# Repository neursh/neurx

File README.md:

# Neurx

A mechanical keyboard aiming for maximum customizability.

## Features (WIP)

- A 75% keyboard (with numpad mode can be toggled).
- 4 programmable keys + 1 knob.
- Firmware is compatible with Raspberry Pi Pico (and Pico W), written in Rust.
- Plug and play, no driver needed, with 1000Hz polling rate.
- Software for Windows, provides better control over programmable keys.

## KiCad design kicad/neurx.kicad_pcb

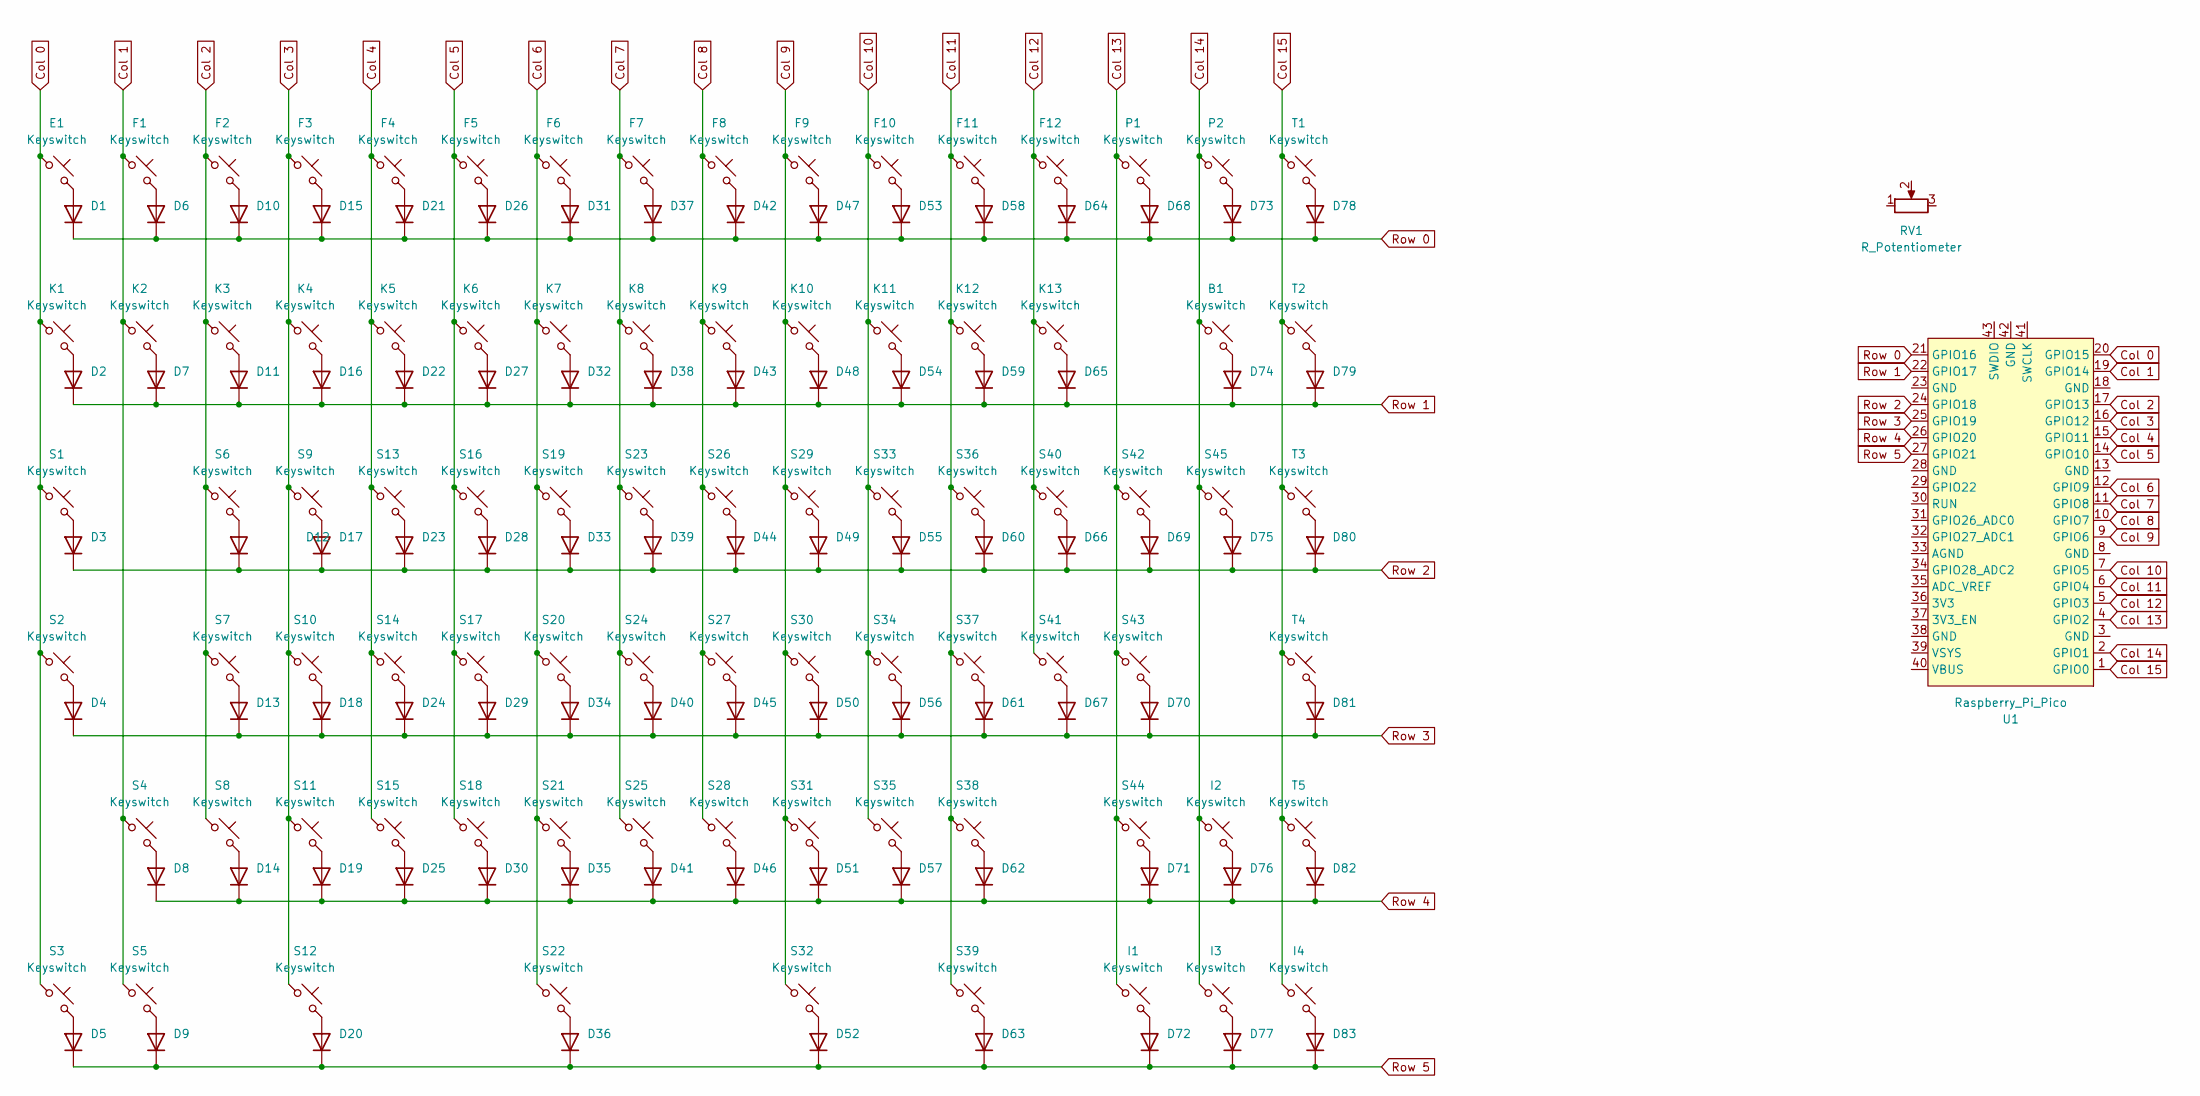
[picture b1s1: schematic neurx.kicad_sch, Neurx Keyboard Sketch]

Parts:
B1: Keyswitch; MX_PCB_2.00u
D1, D2, D3, D4, D5, D6, D7, D8, D9, D10, D11, D12, D13, D14, D15, D16, D17, D18, D19, D20, D21, D22, D23, D24, D25, D26, D27, D28, D29, D30, D31, D32, D33, D34, D35, D36, D37, D38, D39, D40, D41, D42, D43, D44, D45, D46, D47, D48, D49, D50, D51, D52, D53, D54, D55, D56, D57, D58, D59, D60, D61, D62, D63, D64, D65, D66, D67, D68, D69, D70, D71, D72, D73, D74, D75, D76, D77, D78, D79, D80, D81, D82, D83: Diode; Diode_DO-35
E1: Keyswitch; MX_PCB_1.00u
F1, F2, F3, F4, F5, F6, F7, F8, F9, F10, F11, F12: Keyswitch; MX_PCB_1.00u
I1, I2, I3, I4: Keyswitch; MX_PCB_1.00u
K1, K2, K3, K4, K5, K6, K7, K8, K9, K10, K11, K12, K13: Keyswitch; MX_PCB_1.00u
P1, P2: Keyswitch; MX_PCB_1.00u
RV1: R_Potentiometer
S1, S45: Keyswitch; MX_PCB_1.50u
S2, S44: Keyswitch; MX_PCB_1.75u
S3, S5, S12, S32, S39: Keyswitch; MX_PCB_1.25u
S4, S43: Keyswitch; MX_PCB_2.25u
S6, S7, S8, S9, S10, S11, S13, S14, S15, S16, S17, S18, S19, S20, S21, S23, S24, S25, S26, S27, S28, S29, S30, S31, S33, S34, S35, S36, S37, S38, S40, S41, S42: Keyswitch; MX_PCB_1.00u
S22: Keyswitch; MX_PCB_6.25u
T1, T2, T3, T4, T5: Keyswitch; MX_PCB_1.00u
U1: Raspberry_Pi_Pico

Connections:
Col 0: E1.1, K1.1, S1.1, S2.1, S3.1, U1.20 (GPIO15)
Col 1: F1.1, K2.1, S4.1, S5.1, U1.19 (GPIO14)
Col 2: F2.1, K3.1, S6.1, S7.1, S8.1, U1.17 (GPIO13)
Col 3: F3.1, K4.1, S9.1, S10.1, S11.1, S12.1, U1.16 (GPIO12)
Col 4: F4.1, K5.1, S13.1, S14.1, S15.1, U1.15 (GPIO11)
Col 5: F5.1, K6.1, S16.1, S17.1, S18.1, U1.14 (GPIO10)
Col 6: F6.1, K7.1, S19.1, S20.1, S21.1, S22.1, U1.12 (GPIO9)
Col 7: F7.1, K8.1, S23.1, S24.1, S25.1, U1.11 (GPIO8)
Col 8: F8.1, K9.1, S26.1, S27.1, S28.1, U1.10 (GPIO7)
Col 9: F9.1, K10.1, S29.1, S30.1, S31.1, S32.1, U1.9 (GPIO6)
Col 10: F10.1, K11.1, S33.1, S34.1, S35.1, U1.7 (GPIO5)
Col 11: F11.1, K12.1, S36.1, S37.1, S38.1, S39.1, U1.6 (GPIO4)
Col 12: F12.1, K13.1, S40.1, S41.1, U1.5 (GPIO3)
Col 13: I1.1, P1.1, S42.1, S43.1, S44.1, U1.4 (GPIO2)
Col 14: B1.1, I2.1, I3.1, P2.1, S45.1, U1.2 (GPIO1)
Col 15: I4.1, T1.1, T2.1, T3.1, T4.1, T5.1, U1.1 (GPIO0)
unnamed: D1.2 (A), E1.2
unnamed: D2.2 (A), K1.2
unnamed: D3.2 (A), S1.2
unnamed: D4.2 (A), S2.2
unnamed: D5.2 (A), S3.2
unnamed: D6.2 (A), F1.2
unnamed: D7.2 (A), K2.2
unnamed: D8.2 (A), S4.2
unnamed: D9.2 (A), S5.2
unnamed: D10.2 (A), F2.2
unnamed: D11.2 (A), K3.2
unnamed: D12.2 (A), S6.2
unnamed: D13.2 (A), S7.2
unnamed: D14.2 (A), S8.2
unnamed: D15.2 (A), F3.2
unnamed: D16.2 (A), K4.2
unnamed: D17.2 (A), S9.2
unnamed: D18.2 (A), S10.2
unnamed: D19.2 (A), S11.2
unnamed: D20.2 (A), S12.2
unnamed: D21.2 (A), F4.2
unnamed: D22.2 (A), K5.2
unnamed: D23.2 (A), S13.2
unnamed: D24.2 (A), S14.2
unnamed: D25.2 (A), S15.2
unnamed: D26.2 (A), F5.2
unnamed: D27.2 (A), K6.2
unnamed: D28.2 (A), S16.2
unnamed: D29.2 (A), S17.2
unnamed: D30.2 (A), S18.2
unnamed: D31.2 (A), F6.2
unnamed: D32.2 (A), K7.2
unnamed: D33.2 (A), S19.2
unnamed: D34.2 (A), S20.2
unnamed: D35.2 (A), S21.2
unnamed: D36.2 (A), S22.2
unnamed: D37.2 (A), F7.2
unnamed: D38.2 (A), K8.2
unnamed: D39.2 (A), S23.2
unnamed: D40.2 (A), S24.2
unnamed: D41.2 (A), S25.2
unnamed: D42.2 (A), F8.2
unnamed: D43.2 (A), K9.2
unnamed: D44.2 (A), S26.2
unnamed: D45.2 (A), S27.2
unnamed: D46.2 (A), S28.2
unnamed: D47.2 (A), F9.2
unnamed: D48.2 (A), K10.2
unnamed: D49.2 (A), S29.2
unnamed: D50.2 (A), S30.2
unnamed: D51.2 (A), S31.2
unnamed: D52.2 (A), S32.2
unnamed: D53.2 (A), F10.2
unnamed: D54.2 (A), K11.2
unnamed: D55.2 (A), S33.2
unnamed: D56.2 (A), S34.2
unnamed: D57.2 (A), S35.2
unnamed: D58.2 (A), F11.2
unnamed: D59.2 (A), K12.2
unnamed: D60.2 (A), S36.2
unnamed: D61.2 (A), S37.2
unnamed: D62.2 (A), S38.2
unnamed: D63.2 (A), S39.2
unnamed: D64.2 (A), F12.2
unnamed: D65.2 (A), K13.2
unnamed: D66.2 (A), S40.2
unnamed: D67.2 (A), S41.2
unnamed: D68.2 (A), P1.2
unnamed: D69.2 (A), S42.2
unnamed: D70.2 (A), S43.2
unnamed: D71.2 (A), S44.2
unnamed: D72.2 (A), I1.2
unnamed: D73.2 (A), P2.2
unnamed: B1.2, D74.2 (A)
unnamed: D75.2 (A), S45.2
unnamed: D76.2 (A), I2.2
unnamed: D77.2 (A), I3.2
unnamed: D78.2 (A), T1.2
unnamed: D79.2 (A), T2.2
unnamed: D80.2 (A), T3.2
unnamed: D81.2 (A), T4.2
unnamed: D82.2 (A), T5.2
unnamed: D83.2 (A), I4.2
Row 0: D1.1 (K), D6.1 (K), D10.1 (K), D15.1 (K), D21.1 (K), D26.1 (K), D31.1 (K), D37.1 (K), D42.1 (K), D47.1 (K), D53.1 (K), D58.1 (K), D64.1 (K), D68.1 (K), D73.1 (K), D78.1 (K), U1.21 (GPIO16)
Row 1: D2.1 (K), D7.1 (K), D11.1 (K), D16.1 (K), D22.1 (K), D27.1 (K), D32.1 (K), D38.1 (K), D43.1 (K), D48.1 (K), D54.1 (K), D59.1 (K), D65.1 (K), D74.1 (K), D79.1 (K), U1.22 (GPIO17)
Row 2: D3.1 (K), D12.1 (K), D17.1 (K), D23.1 (K), D28.1 (K), D33.1 (K), D39.1 (K), D44.1 (K), D49.1 (K), D55.1 (K), D60.1 (K), D66.1 (K), D69.1 (K), D75.1 (K), D80.1 (K), U1.24 (GPIO18)
Row 3: D4.1 (K), D13.1 (K), D18.1 (K), D24.1 (K), D29.1 (K), D34.1 (K), D40.1 (K), D45.1 (K), D50.1 (K), D56.1 (K), D61.1 (K), D67.1 (K), D70.1 (K), D81.1 (K), U1.25 (GPIO19)
Row 4: D8.1 (K), D14.1 (K), D19.1 (K), D25.1 (K), D30.1 (K), D35.1 (K), D41.1 (K), D46.1 (K), D51.1 (K), D57.1 (K), D62.1 (K), D71.1 (K), D76.1 (K), D82.1 (K), U1.26 (GPIO20)
Row 5: D5.1 (K), D9.1 (K), D20.1 (K), D36.1 (K), D52.1 (K), D63.1 (K), D72.1 (K), D77.1 (K), D83.1 (K), U1.27 (GPIO21)

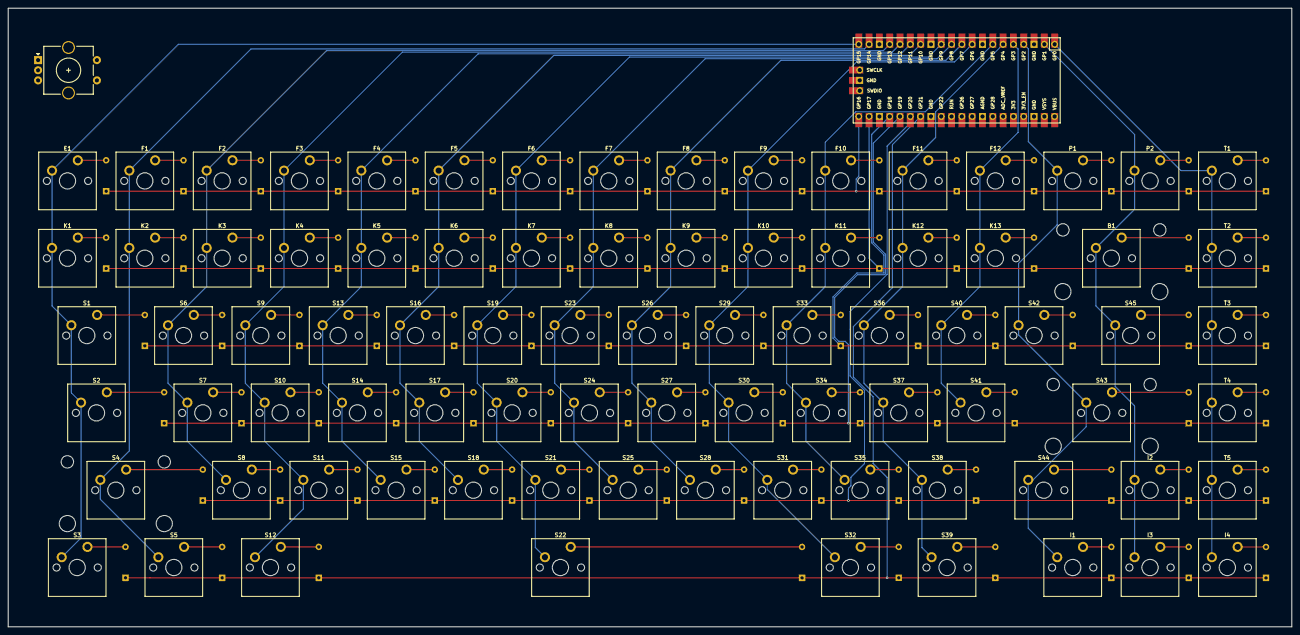
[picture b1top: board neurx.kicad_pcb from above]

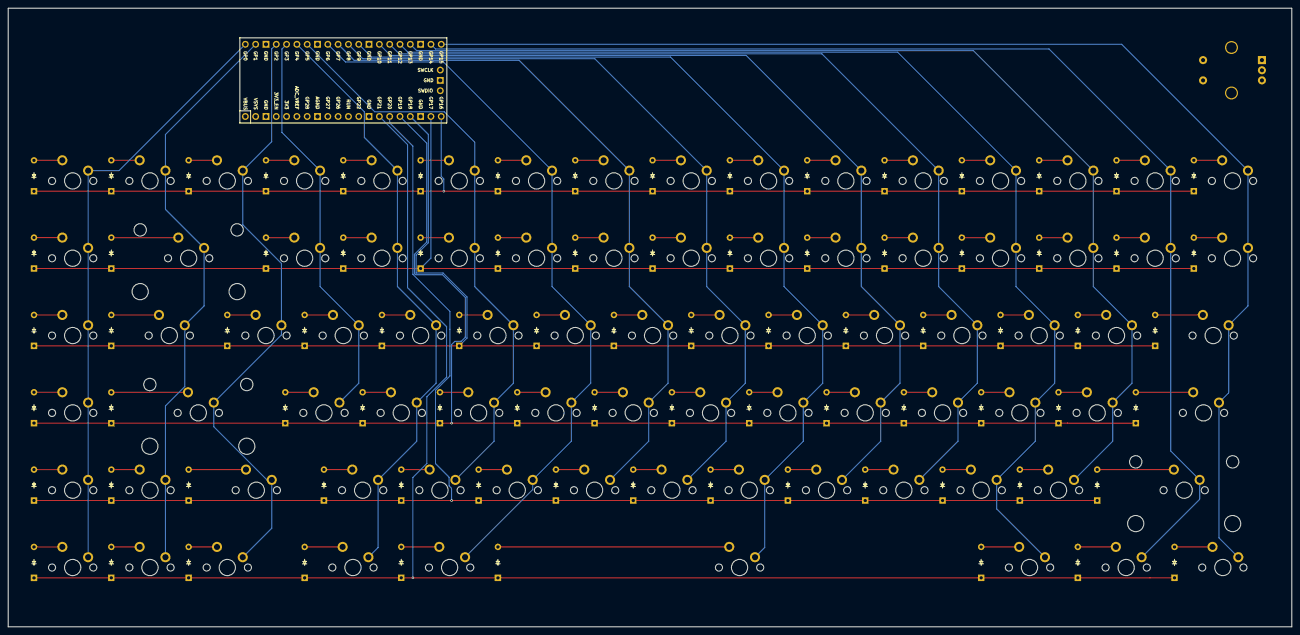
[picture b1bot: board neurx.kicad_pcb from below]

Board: 2 copper layers, 316.2 x 152.4 mm, 167 parts (83 on the bottom side), 105 nets.

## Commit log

2025-01-07 Controller for keyboard
2025-01-07 Move the controller folder out to main
2025-01-07 Rename neursx.json to neurx.json
2025-01-07 Set build target
2025-01-07 Add prettier and heapless to replace some std structures
2025-01-07 Matrix scheme
2025-01-08 Add keycode struct
2025-01-08 Implementing matrix scanning
2025-01-08 Add USB runner
2025-01-08 Plug row 5 to pico, completely forgot that
2025-01-08 Update design from sketch
2025-01-08 It's not json
2025-01-08 Allows `dead_code`, it's just unused keys
2025-01-08 Doesn't work without these features, pls don't ask
2025-01-08 Rename, changes how the struct initialization work, and implement scanning, might find a faster way to do
2025-01-08 Provide the struct with columns and rows to avoid ownership problems, finish implementation
2025-01-08 Change dummy serial number
2025-01-09 Use `count_ones` for checking modifier key
2025-01-09 Report using reference, avoid creating a new array for each scan.
2025-01-13 Make things more clear
